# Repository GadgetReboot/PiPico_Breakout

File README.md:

# PiPico_Breakout
RPi Pico Breakout board<BR><BR>
<br><br>

This breakout board provides labeled RPi headers including extra 3.3V, VBUS and GND pins.<br>
There is also a power LED and a convenient reset button for the Pi Pico.<br><br>  
Pi Pico KiCad symbols and footprints are from https://github.com/ncarandini/KiCad-RP-Pico<BR> 
Pi Pico Datasheet:  https://datasheets.raspberrypi.com/pico/pico-datasheet.pdf<BR><BR>

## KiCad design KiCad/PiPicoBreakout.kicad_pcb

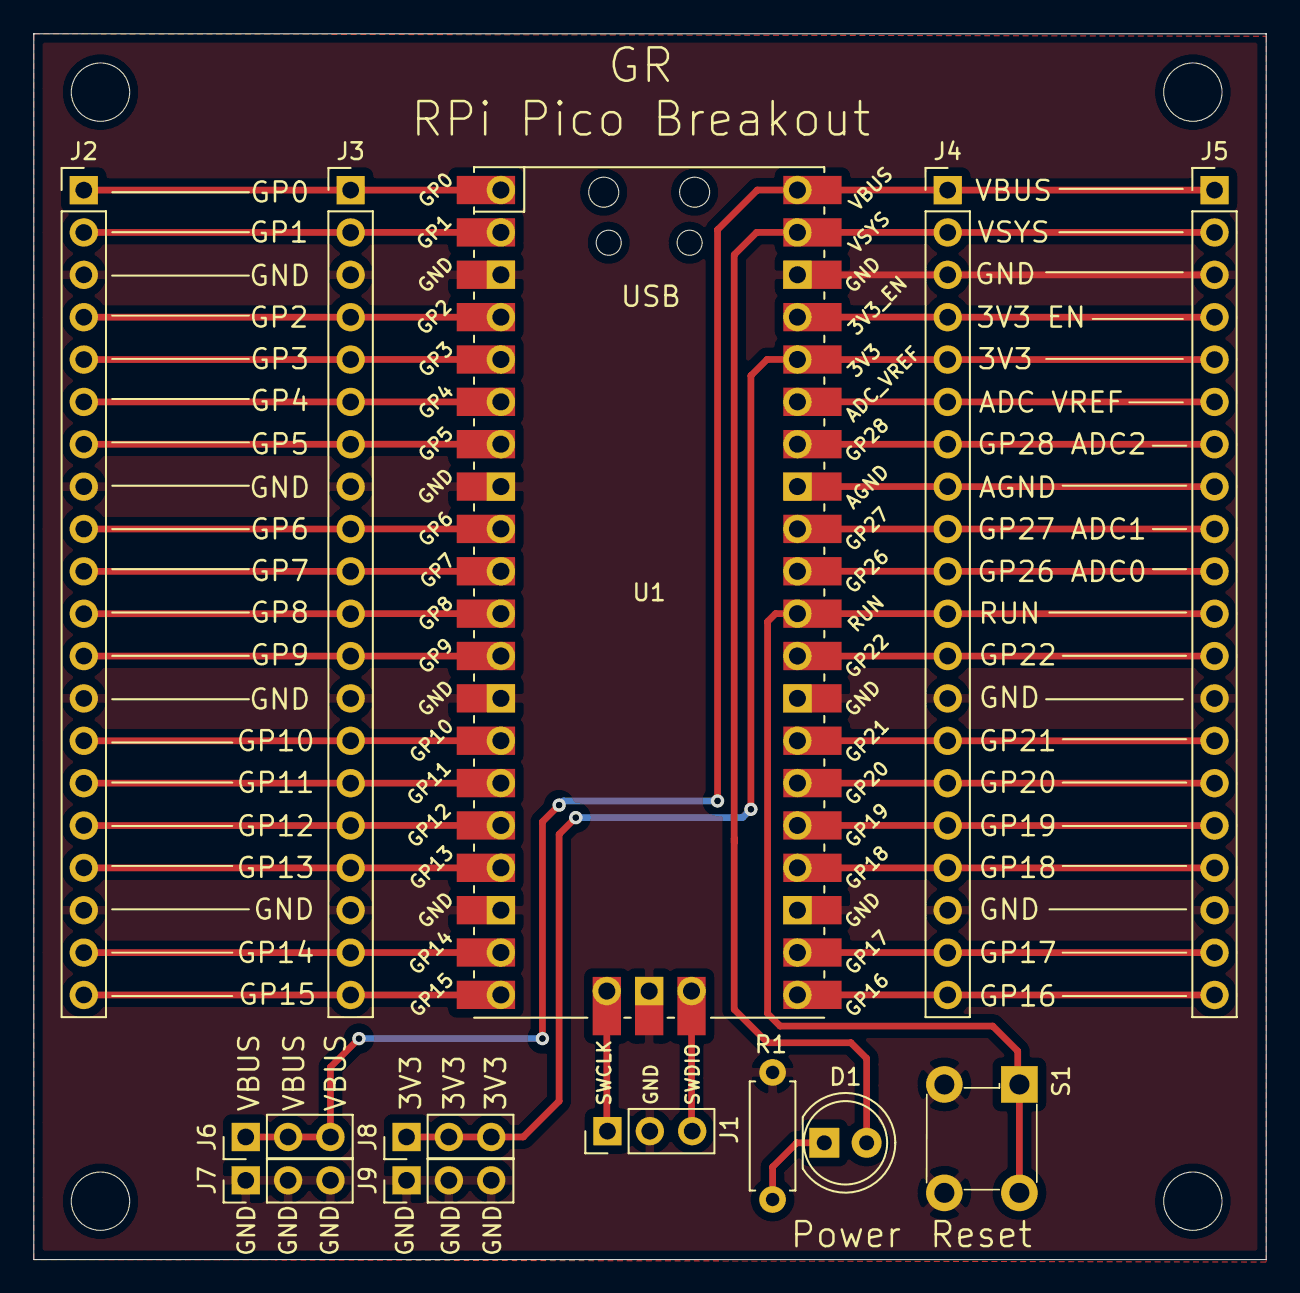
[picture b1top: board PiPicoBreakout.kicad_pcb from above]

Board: 2 copper layers, 73.9 x 73.5 mm, 17 parts (0 on the bottom side), 37 nets.

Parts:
D1: LED_Small_ALT; LED_D5.0mm_Clear
H1, H2, H3, H4: MountingHole; MountingHole_3.5mm
J1, J6, J7, J8, J9: UART; PinHeader_1x03_P2.54mm_Vertical
J2, J3, J4, J5: Conn_01x20; PinHeader_1x20_P2.54mm_Vertical
R1: 2K; R_Axial_DIN0207_L6.3mm_D2.5mm_P7.62mm_Horizontal
S1: 1825910-6; Switch_Tactile_THT_6x6mm
U1: Pico; RPi_Pico_SMD_TH

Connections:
/3V3: J4.5, J5.5, J8.1, J8.2, J8.3, U1.36
/3V3_EN: J4.4, J5.4, U1.37
/ADC_VREF: J4.6, J5.6, U1.35
/AGND: J4.8, J5.8, U1.33
/GP0: J2.1, J3.1, U1.1
/GP1: J2.2, J3.2, U1.2
/GP2: J2.4, J3.4, U1.4
/GP3: J2.5, J3.5, U1.5
/GP4: J2.6, J3.6, U1.6
/GP5: J2.7, J3.7, U1.7
/GP6: J2.9, J3.9, U1.9
/GP7: J2.10, J3.10, U1.10
/GP8: J2.11, J3.11, U1.11
/GP9: J2.12, J3.12, U1.12
/GP10: J2.14, J3.14, U1.14
/GP11: J2.15, J3.15, U1.15
/GP12: J2.16, J3.16, U1.16
/GP13: J2.17, J3.17, U1.17
/GP14: J2.19, J3.19, U1.19
/GP15: J2.20, J3.20, U1.20
/GP16: J4.20, J5.20, U1.21
/GP17: J4.19, J5.19, U1.22
/GP18: J4.17, J5.17, U1.24
/GP19: J4.16, J5.16, U1.25
/GP20: J4.15, J5.15, U1.26
/GP21: J4.14, J5.14, U1.27
/GP22: J4.12, J5.12, U1.29
/GP26_ADC0: J4.10, J5.10, U1.31
/GP27_ADC1: J4.9, J5.9, U1.32
/GP28_ADC2: J4.7, J5.7, U1.34
/RUN: J4.11, J5.11, S1.1, S1.2, U1.30
/SWCLK: J1.1, U1.41
/SWDIO: J1.3, U1.43
/VBUS: J4.1, J5.1, J6.1, J6.2, J6.3, U1.40
/VSYS: D1.2, J4.2, J5.2, U1.39
GND: J1.2, J2.3, J2.8, J2.13, J2.18, J3.3, J3.8, J3.13, J3.18, J4.3, J4.13, J4.18, J5.3, J5.13, J5.18, J7.1, J7.2, J7.3, J9.1, J9.2, J9.3, R1.2, S1.3, S1.4, U1.3, U1.8, U1.13, U1.18, U1.23, U1.28, U1.38, U1.42
unnamed: D1.1, R1.1
